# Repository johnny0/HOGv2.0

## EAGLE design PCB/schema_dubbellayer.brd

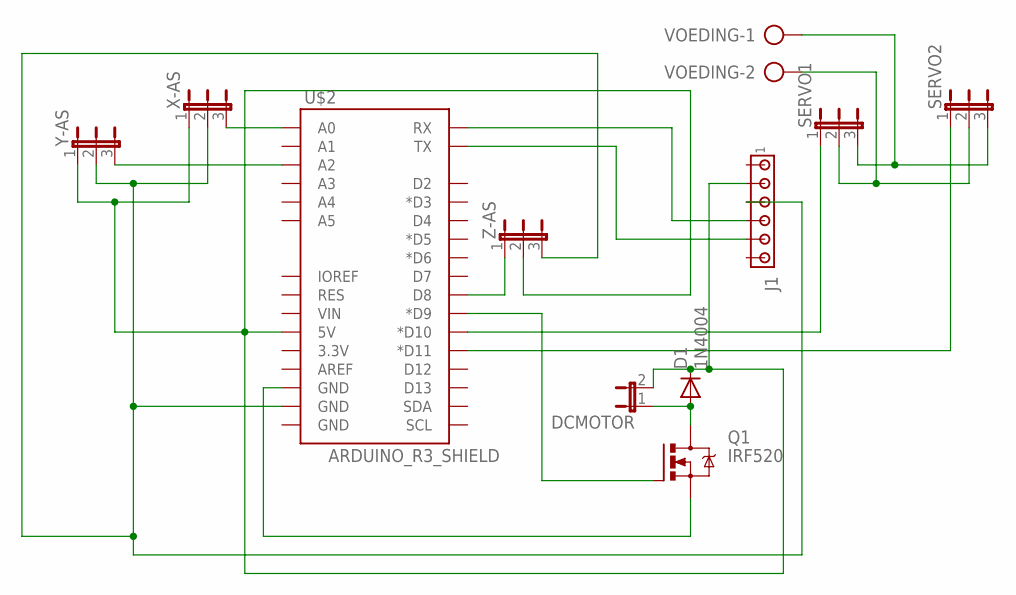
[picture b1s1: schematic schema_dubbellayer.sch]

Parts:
D1: 1N4004; DO41-10
DCMOTOR: JP1E; JP1
J1: MTA06-100; 10X06MTA
Q1: IRF520; TO220BV
SERVO1, SERVO2: JP2E; JP2
U$2: ARDUINO_R3_SHIELD; UNO_R3_SHIELD
VOEDING: AK300/2
X-AS: JP2E; JP2
Y-AS: JP2E; JP2
Z-AS: JP2E; JP2

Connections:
unnamed: U$2.A0, X-AS.3
unnamed: U$2.A2, Y-AS.3
unnamed: D1.A, DCMOTOR.1, Q1.D
unnamed: J1.4 (3), U$2.GND@1 (GND), X-AS.2, Y-AS.2, Z-AS.3
unnamed: Q1.G, U$2.D9 (*D9)
unnamed: Q1.S, U$2.GND@2 (GND)
unnamed: U$2.D8, Z-AS.1
unnamed: SERVO1.1, U$2.D10 (*D10)
unnamed: SERVO2.1, U$2.D11 (*D11)
unnamed: D1.C, DCMOTOR.2, J1.5 (2), U$2.5V, X-AS.1, Y-AS.1, Z-AS.2
unnamed: SERVO1.2, SERVO2.2, VOEDING.2
unnamed: SERVO1.3, SERVO2.3, VOEDING.1
unnamed: J1.2 (5), U$2.TX
unnamed: J1.3 (4), U$2.RX

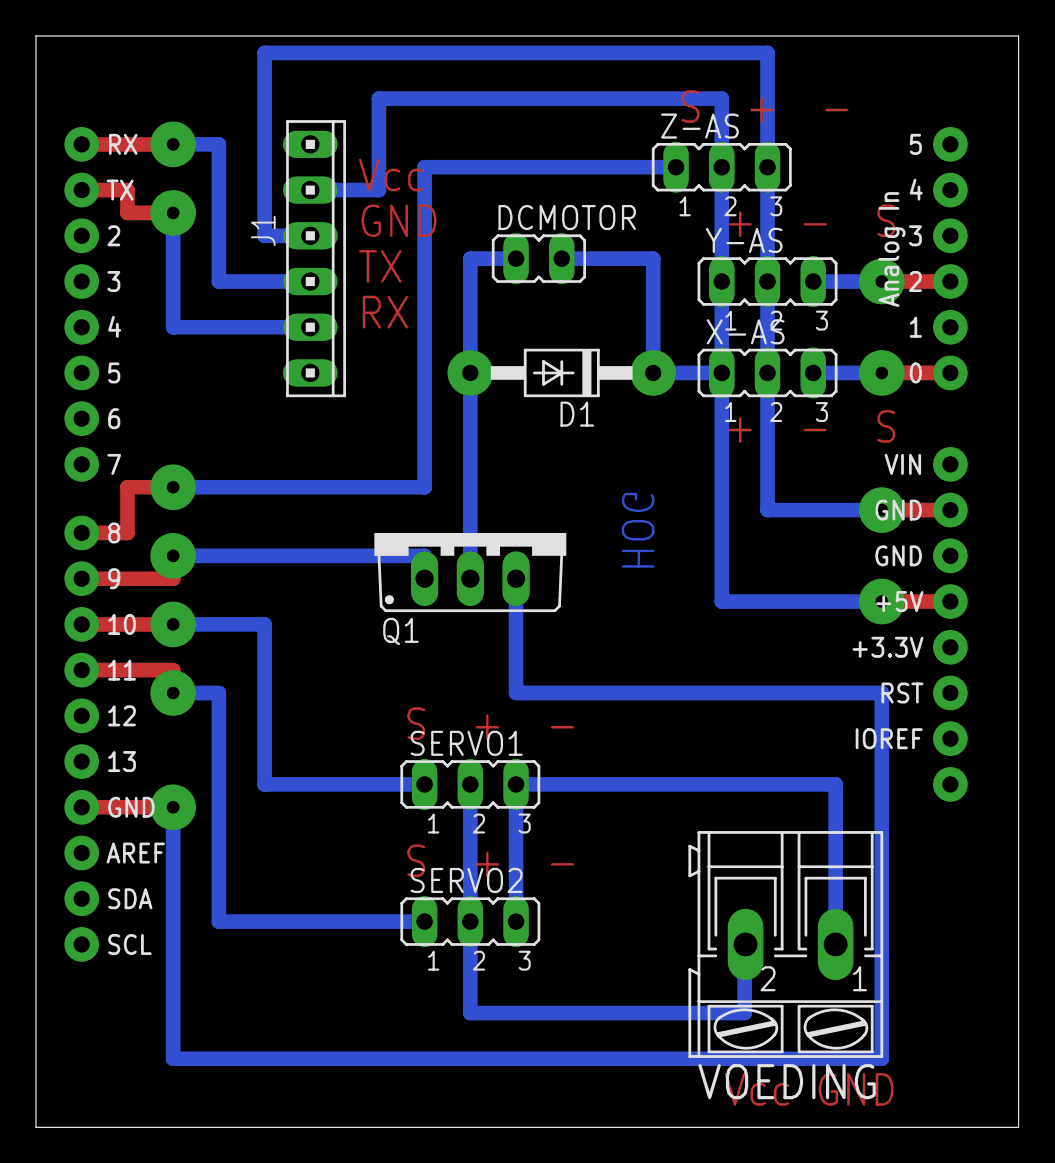
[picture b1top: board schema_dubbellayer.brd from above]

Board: 2 copper layers, 54.6 x 60.6 mm, 11 parts (0 on the bottom side), 14 nets.

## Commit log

2014-12-18 timelapse
2014-12-18 test
2014-12-18 Transmitter software in LabVIEW
2014-12-18 Reciever software in Arduino IDE
2014-12-18 PCB layout
2014-12-18 afgewerkte hog
2014-12-18 Hardware

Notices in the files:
parts and their libraries:
SparkFun-Boards: Licensing: CC v3.0 Share-Alike You are welcome to use this library for commercial purposes.
